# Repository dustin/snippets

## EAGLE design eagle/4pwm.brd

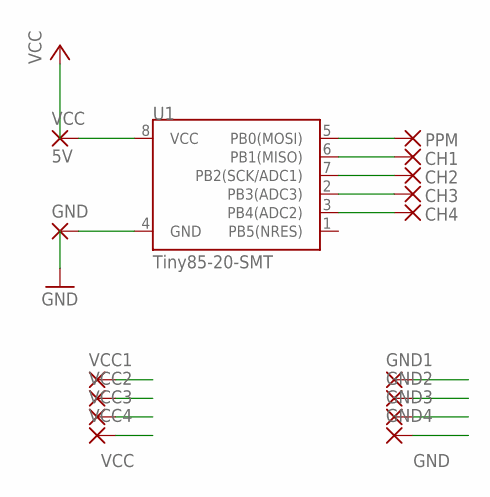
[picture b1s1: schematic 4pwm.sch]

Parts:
CH1, CH2, CH3, CH4: SMD2; SMD1,27-2,54
GND, GND1, GND2, GND3, GND4: SMD2; SMD1,27-2,54
PPM: SMD2; SMD1,27-2,54
U1: Tiny85-20-SMT; SO08-EIAJ
VCC: 5V; SMD1,27-2,54
VCC1, VCC2, VCC3, VCC4: SMD2; SMD1,27-2,54

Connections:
GND: GND.1, GND1.1, GND2.1, GND3.1, GND4.1, U1.4 (GND)
unnamed: PPM.1, U1.5 (PB0(MOSI))
unnamed: CH1.1, U1.6 (PB1(MISO))
unnamed: CH2.1, U1.7 (PB2(SCK/ADC1))
unnamed: CH3.1, U1.2 (PB3(ADC3))
unnamed: CH4.1, U1.3 (PB4(ADC2))
VCC: U1.8 (VCC), VCC.1, VCC1.1, VCC2.1, VCC3.1, VCC4.1

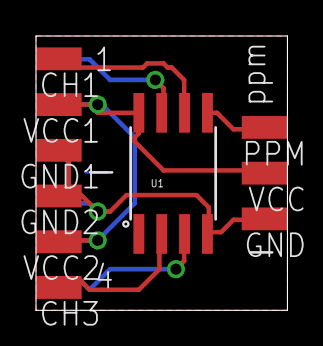
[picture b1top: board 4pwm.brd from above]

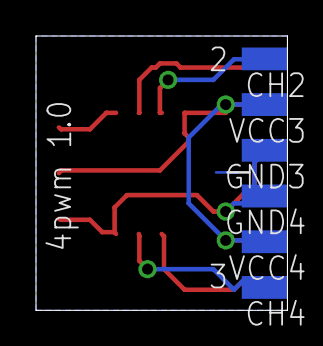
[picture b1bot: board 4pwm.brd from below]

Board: 2 copper layers, 14.0 x 15.2 mm, 16 parts (6 on the bottom side), 7 nets.

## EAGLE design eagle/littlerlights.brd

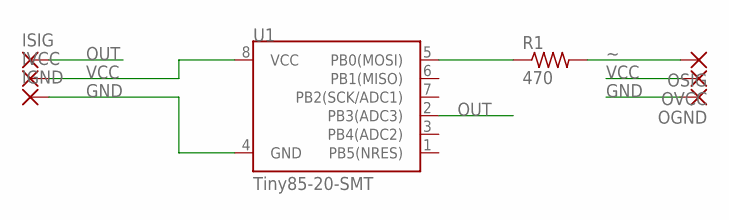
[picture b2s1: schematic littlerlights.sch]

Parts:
IGND: SMD2; SMD1,27-2,54
ISIG: SMD2; SMD1,27-2,54
IVCC: SMD2; SMD1,27-2,54
OGND: SMD2; SMD1,27-2,54
OSIG: SMD2; SMD1,27-2,54
OVCC: SMD2; SMD1,27-2,54
R1: 470; R0603; DIGIKEY MCT0603-470-CFCT-ND
U1: Tiny85-20-SMT; SO08-EIAJ; DIGIKEY ATTINY85-20SHRCT-ND

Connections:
GND: IGND.1, OGND.1, U1.4 (GND)
MOSI: R1.1, U1.5 (PB0(MOSI))
OUT: ISIG.1, U1.2 (PB3(ADC3))
VCC: IVCC.1, OVCC.1, U1.8 (VCC)
~: OSIG.1, R1.2

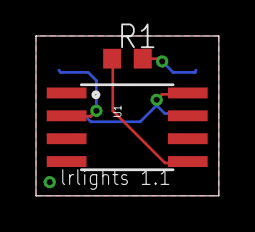
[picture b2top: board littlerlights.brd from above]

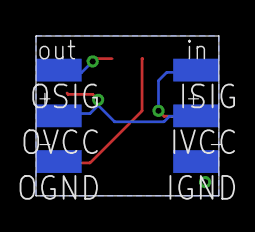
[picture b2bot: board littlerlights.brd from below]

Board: 2 copper layers, 10.2 x 8.9 mm, 8 parts (6 on the bottom side), 5 nets.

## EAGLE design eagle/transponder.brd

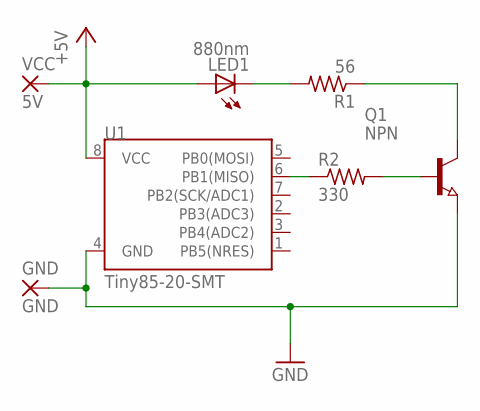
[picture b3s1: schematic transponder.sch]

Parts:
GND: GND; SMD1,27-2,54
LED1: 880nm; LED3MM
Q1: NPN; SOT23
R1: 56; R0603
R2: 330; R0603
U1: Tiny85-20-SMT; SO08-EIAJ
VCC: 5V; SMD1,27-2,54

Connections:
+5V: LED1.A, U1.8 (VCC), VCC.1
GND: GND.1, Q1.2 (E), U1.4 (GND)
unnamed: R2.1, U1.6 (PB1(MISO))
unnamed: Q1.1 (B), R2.2
unnamed: LED1.K (C), R1.2
unnamed: Q1.3 (C), R1.1

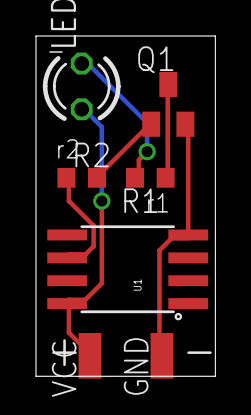
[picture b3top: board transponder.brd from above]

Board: 2 copper layers, 10.0 x 18.9 mm, 7 parts (0 on the bottom side), 6 nets.

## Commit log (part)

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2015-07-01 littlelights as shipped
2015-07-01 Ignore eagle board and schema backups
2015-07-02 Failsafe monitor tool
2015-07-02 Disable with a button
2015-07-05 Passively parse MSP messages on their way to the OSD
2015-07-05 Can now enable/disable parsing of chunks based on interest
2015-07-05 Need those BOXIDs
2015-07-05 Don't blink on arm/disarm commands
2015-07-05 Inline state callbacks
2015-07-05 Add error callbacks
2015-07-05 Rename crc failed callback since it's not CRC
2015-07-05 Don't need the == and #else there
2015-07-05 Go ahead and inline status and rc callbacks since they're trivial now
2015-07-05 Sped up the tracking code enough to be somewhat usable
2015-07-06 Disallow MSP copy and assign
2015-07-07 Return the amount of stuff removed so mail works
2015-07-21 Remove MSP reference from serial sample
2015-08-05 Notes on motor testing
2015-08-23 Read a couple values in raw
2015-08-23 cosmetic updates
2015-08-23 Much lower power draw
2015-08-28 Fix longer polling.
    I discovered these timers I'm using are 16-bit millis. Won't do if I
    want to go longer.
2015-08-28 Log time since last message
2015-08-28 Start with a non-wrapping low
2015-10-10 MSP API cleanup
2015-10-10 Cleaner C API and insides for MSP
2015-10-12 Add an OSD capture for testing
2015-10-14 Handle bidirectional MSP
2015-10-26 Simplify MSP buffer management and stuff
2015-11-14 Mirror the whole drive structure with the drop folder
2016-01-27 fujotime
2016-01-27 Cleaned up silks for fujotime
2016-03-03 Working blink
2016-03-04 External on/off signaler thread
2016-03-14 Hue Wheel Project
2016-03-14 Make the little lights actually little
2016-03-14 Update wiring comment
2016-03-14 Change high/low out of range handling.
    Default to defaults in eeprom reading instead of fresh rediscovery.
    If no valid pulse for three seconds, reset the edges.
2016-03-15 Fix loading to not be wrong/insane
2016-03-15 Functioning black
2016-03-15 Simplify color/black setting
    CRGB has a setHue which is convenient.
    Just set it on pixel 0 and then copy that across the rest.
2016-03-15 Consistency in declaring variables
2016-03-15 Don't even bother declaring pixels with showColor
2016-03-17 Make persistence (to EEPROM) configurable
2016-03-18 forward declarations for compilation of cannedlights
2016-03-22 Working with openocd
2016-03-23 Functional openocd config with chibios
    I copied this from the stm32f0x.cfg, but with -rtos ChibiOS
2016-03-31 Various SUMD bug fixes.
    Almost works a little.
2016-04-01 Parse sumd stream from a csv export from Logic
2016-04-01 demo needs to transmit more frequently
2016-04-05 Added megacommit script I use for gathering objects.
2016-04-07 Parse binary sumd
2016-04-09 Fix typo and document what PERSIST works around
2016-04-15 Simple avr blink demo for micronucleus
    (which, for whatever reason, won't blink on my stupid digispark, even
    using a program that previously did)
2016-04-15 Use ports for arduino timer blinks
2016-04-15 Abstracted out wd_control
2016-04-16 Use built-in CRC
2016-04-16 Replace byte with uint8_t
    Also, use malloc instead of new
2016-04-19 Predeclare for compile fixes
2016-04-20 Did some testing on the failsafe.
    So like, now the code does what I mean.
2016-04-20 whitespace fix
2016-04-20 Run disabling code out of the ISR instead of the loop
2016-04-20 We don't need button-watching variable.
2016-04-20 Check pin change on both pins
2016-04-21 watchdog ISR can be naked
2016-04-21 Remove a couple unused headers
2016-04-21 Stupid tab
2016-04-21 overflow counter as uint8_t
    This reduced the size from 298 bytes to 282. 'int' involves a bunch of
    instructions to deal with two byte numbers that uint8_t doesn't have to
    deal with.
2016-04-21 Added myself a convenient asm output target
2016-04-21 Clear all the interrupts and timer configs at once
    Gets us down to 270 bytes
2016-04-23 failsafe in asm
2016-04-23 prevb and overflows in registers
2016-04-23 Don't clear bss or copy data
2016-04-26 PPM -> PWM decoder
2016-04-26 PPM -> PWM in asm
2016-04-26 Precalculate the pin position.
    Instead of doing this in a loop, do it when it changes. We know this.
2016-04-26 Fix up my labels
2016-04-26 Just set all the register bits exactly how I want them.
2016-04-26 Disable sleep mode -- it's 4 cycles
2016-04-27 Got my jump backwards
2016-04-29 PPM using overflow and a comparator.
    I used overflow here because I originally wrote this for an 8-bit timer,
    but switched to a 16-bit timer to be a little easier to get my initial pass.
2016-04-30 Implement ppm transmission with comp a and b
2016-05-01 More dynamically compute the inter-pulse gap
2016-05-03 4pwm hardware
2016-05-03 Fixed up the labels to match reality
2016-05-03 My parts library.
2016-05-05 Fixed connections on 662
2016-08-10 s.port sniffer decoder thing
2016-08-11 Dump out messages that weren't understood more clearly
2016-08-22 Doh, need O_WRONLY
    (also, os.O_CREATE == syscall.O_CREAT)
2016-09-16 Bike LED controller
2016-09-17 I only had 60 lights on a strip.
    (and only enough RAM for something less than 100)
2016-10-06 Stupid avconv lacking -o ...
2016-11-10 parametric half cube box
2016-11-10 Don't need a faces var anymore
2016-11-10 Added a nail mount thing
2016-11-12 vase vs. vase_with_nailmount as toplevel modules
2016-12-18 Added some countersunk screw holes and more support
2016-12-19 Fixing up some scaling properties
2016-12-20 scad cheese
2016-12-21 Make useful variables for thingiverse customizer
2016-12-22 One strategy for a conic round pot.
2017-01-02 Don't do the nail mount by default.
2017-01-03 Trying out a diamond shaped pot
2017-01-04 Little bit thicker diamond
2017-01-10 Moon vase
2017-02-05 xt30 cap
2017-02-05 This seems to print a nice xt30 connector
2017-02-06 Cleaned up and printed
2017-02-28 Start in the proper orientation.
2017-03-01 Planter ring
2017-03-06 Make the diamond planter customizable.
2017-03-08 openscad version of my wire holder
2017-03-08 More parameteric and with conditional minkowski
2017-03-08 I guess the braces are important, too.
2017-03-09 Use $fa and $fs instead of $fn
2017-03-09 S800 electronics pod
2017-03-09 With a cheap way to round the edges of the main plate
2017-03-09 Increase structural integrity of the FC mount slightly
2017-03-09 Ignore a few bits of junk in here
2017-03-10 z spinner I came up with on the bus this morning
    I have no use for this, but a friend mentioned one for his son and I
    threw this together real quick.
2017-03-11 How to fillet with a 2D drawing
2017-03-12 Final print was slightly smaller than original design
2017-03-22 Made some adjustments for final bearing caps
2017-03-30 Shrink the s800 plate to fit between the shoulders.
2017-04-05 An XT60 model
2017-04-11 Stand for RF Explorer
    Modeled after http://www.thingiverse.com/thing:754510 -- but without
    the little hook things that won't fit with my sleeve on.
    Using line primitives from https://github.com/JustinSDK/dotSCAD
    I basically used the line primitives and just sort of traced the
    original thing. I feel like I could do a lot better if I did some
    math.
2017-04-11 Don't render the parts so far apart
2017-04-11 Got rid of unnecessary line/polyline stuff.
    Made all configurable on thingiverse
2017-04-11 Name most of the numbers.
2017-04-12 Use my line module to draw theh sine at a specific thickness
2017-04-24 Battery box I made for the neighbor's birthday
2017-05-28 qavcam2: mounted from the further back standoffs
2017-05-29 LCD screen to gopro adaptor
2017-05-31 GoPro -> clamp mount
2017-06-01 draft of hs1177 mount for frogger cam
2017-06-02 Updated frogger cam mount for installation.
    I actually think it's *slightly* off in a couple of ways, but it'll
    work.
    Could be a little narrower all around. The standoffs are just barely
    too far out. The actual frogger standoffs are themselves narrower
    than the nylon ones I like to use.
    Also, the actual part the holds the camera feels looser than
2017-07-06 Various tripod stuff
2017-08-31 Return the values of the previous row when adding a new row.
2017-09-07 Euler9
2017-09-07 Euler11
2017-09-07 euler 12
2017-09-07 Fix 1.hs to give the correct answer for the exact argument
2017-09-07 euler 14
2017-09-07 euler 15
2017-09-07 euler 17
2017-09-07 I don't need that zero case if I'm not supporting zero
2017-09-07 Document numwords a bit
2017-09-08 euler 20
2017-09-08 euler 22
2017-09-08 euler 23
2017-09-08 Forgot to check in euler 19 while moving stuff around
2017-09-08 I did euler 24 in ghci directly, but pasted it into a file anyway
2017-09-08 euler 25
2017-09-09 Euler 27
2017-09-10 I solved euler 28 by thinking. Weird...
2017-09-10 euler 30
2017-09-11 euler 32
2017-09-11 concatMap is a lot more satisfying than seemingly repeating the same thing
2017-09-11 euler 34
2017-09-11 euler 36
2017-09-11 euler 37
2017-09-11 use euler lib for 37
2017-09-11 euler lib for 35
2017-09-11 Use euler lib for 34
    Also, went back to more simple types. Probably slower, but things
    work more.
2017-09-11 euler lib for 30
2017-09-11 lib for 25
    Added fib
2017-09-11 euler lib for 3
2017-09-11 Use euler lib for 21.
    This is like, 100x faster.
2017-09-11 euler 20 is basically just euler lib
2017-09-11 lib for 15
2017-09-11 lib for 10
2017-09-11 lib for 7
2017-09-12 euler 38
2017-09-12 euler 40
2017-09-12 Added is_pandigital_n to euler lib
2017-09-12 euler 42
2017-09-12 Factor tests and use Test.QuickCheck.Modifiers
2017-09-12 euler 43
2017-09-13 euler 44
    It's pretty slow, but I don't want to do smarter stuff.
2017-11-23 Some functor exercises
2018-05-14 Pyramid planter
2018-05-14 advent day 2
2018-05-14 Made a little power pole bracket.
2018-05-14 A box for my DPS3005
2018-05-14 prefer . to $ in haskell snippets
2018-05-14 Minor tweak to the cable holder.
2018-06-14 A bit of commentary on my logic puzzle thing.
2018-07-24 Added function to clean up DriveFS trash.
2018-07-27 Some cleanup cleanups
2018-08-04 Document parameters.
2018-08-04 Better customizer doc for smoothing
2018-08-04 Make the drill hole customizable as well.
2018-08-05 Fix the period-to-c function.
    I'd screwed up the most important bit of math in here while trying to
    get everything else right.
2018-08-31 XKCD coaster.
2018-09-02 Sensor display aparatus.
2018-09-03 Abstracted Widget slightly.
2018-09-03 Getting time on the display.
2018-09-03 Display the ages of readings.
2018-09-03 Draw a bit less.
2018-09-04 Use WiFiMulti
2018-09-04 Show wifi status instead the boring IP address.
2018-09-08 Disable the backlight most of the time.
    It's enabled for 15s after data changes, or when someone touches it to
    see what's going on.
    I should probably specify when to turn it off instead of when
    something interesting happened. This would allow errors to display
    longer than data.
    The light pad is jumped to pin 21 via a 0Ω resistor. Convenient fit,
2018-09-08 Added a widget to show battery level.
    TIL the huzzah esp32 has a battery charging circuit and VBAT on A13.
2018-09-08 Trim some serial debug
2018-09-25 Change MQTT client (also got SSL working, kind of unrelated)
2018-09-25 Display OTA updates
2018-09-25 Don't let the error hang over onto the bottom row
2018-10-02 Show more detailed information about wifi when doing wifi stuff.
2019-01-15 some dangling openscad projects
2019-01-15 Added allOf
2019-01-15 monty hall in quickcheck
2019-01-15 Playing around in haskellbook
2019-05-23 Use <$> instead of map ... $
2021-09-01 aqimeter for magtag
2021-09-01 Use MQTT for aqi meter
2021-09-01 Dynamically configurable update periods.
    Probably, it doesn't confirm it picks it up, but it worksish.
2021-09-01 Go back to sleep on any crash.
    I found the unit sitting at a stack trace one day, which wasn't great
    for battery life.
2021-09-01 Use a pm25 adaptor if found
2021-09-01 Watchdog updates.
    I saw a display hanging while trying to connect to the network. Not
    sure how long it was like that, but if it can't get data quickly, it
    should just go back to sleep and try later.
    Cool thing, though, is I had a major network outage after this and it
    did all the right things.
2021-09-02 If we have a local AQI, display it.
2021-09-03 If voltage is high, don't sleep so long.
    e.g., when we're plugged in
2021-10-09 If i2c can't initialize, just don't use it.
2022-12-03 aqimeter update
2022-12-29 Stop refreshing the display when I'm not there
2022-12-31 Better button handling
    And don't reschedule if we happen to reinit
2025-03-04 Updated my display for stability
2026-01-02 Direction meter prototype
2026-01-03 Fix up my direction brightness
2026-02-14 An XT90 cover
2026-02-20 Added BOSL2 submodule for openscad

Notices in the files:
parts and their libraries:
SparkFun-DigitalIC: Licensing: Creative Commons ShareAlike 4.0 International - https://creativecommons.org/licenses/by-sa/4.0
